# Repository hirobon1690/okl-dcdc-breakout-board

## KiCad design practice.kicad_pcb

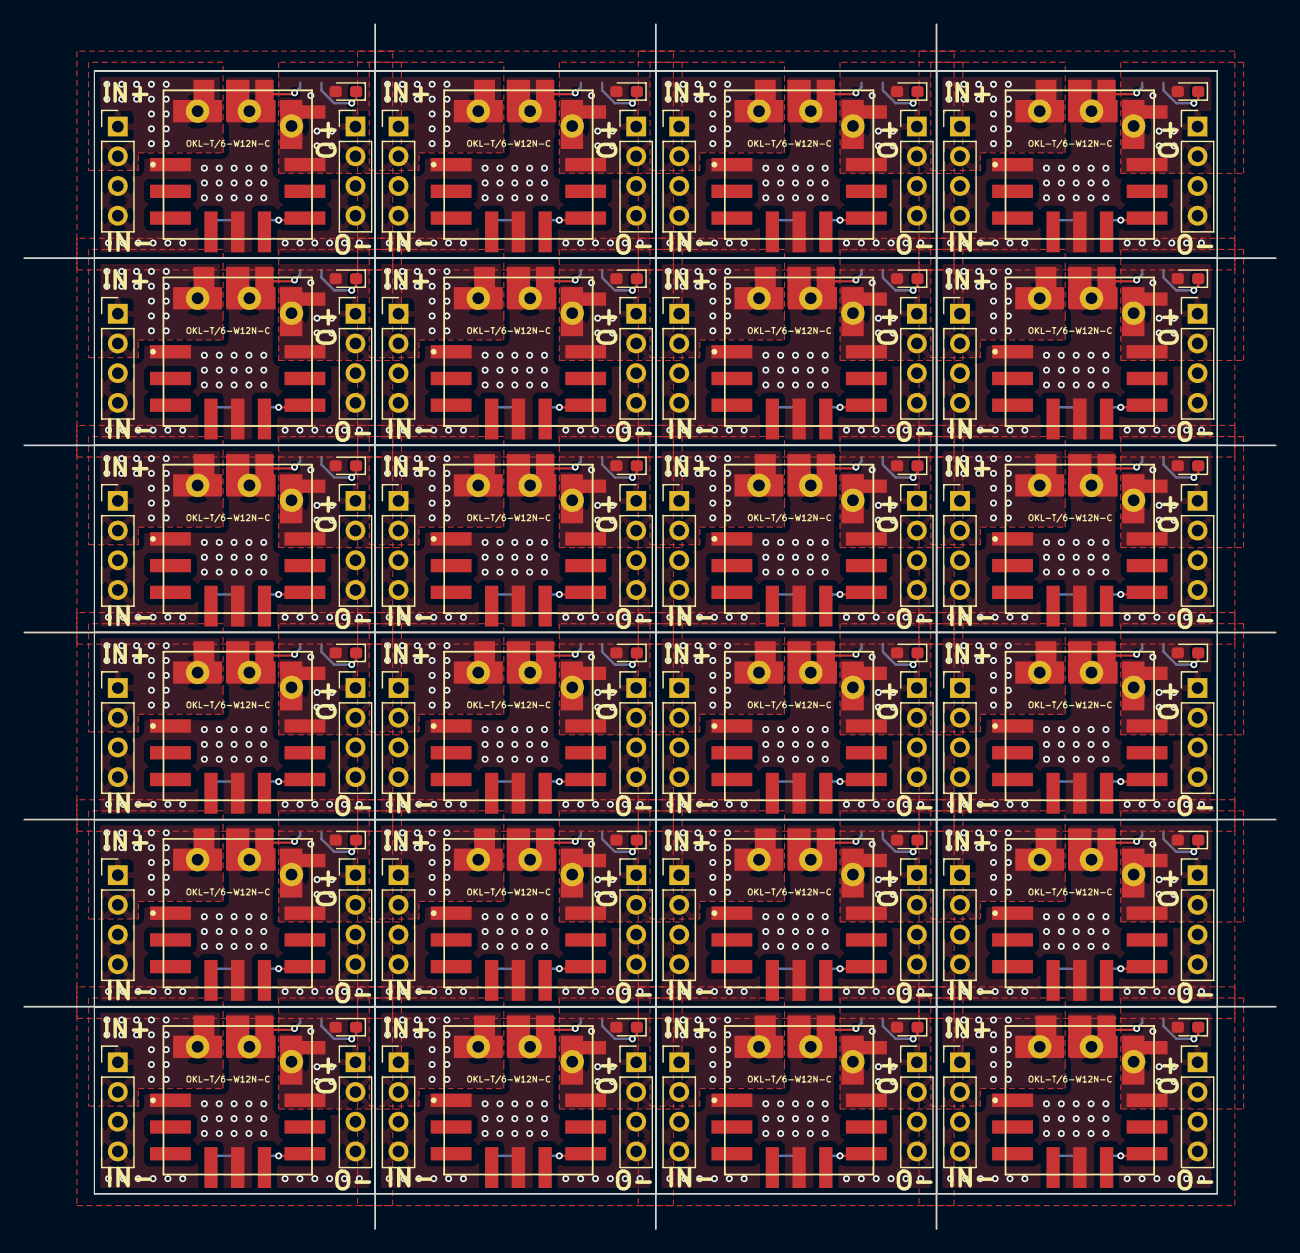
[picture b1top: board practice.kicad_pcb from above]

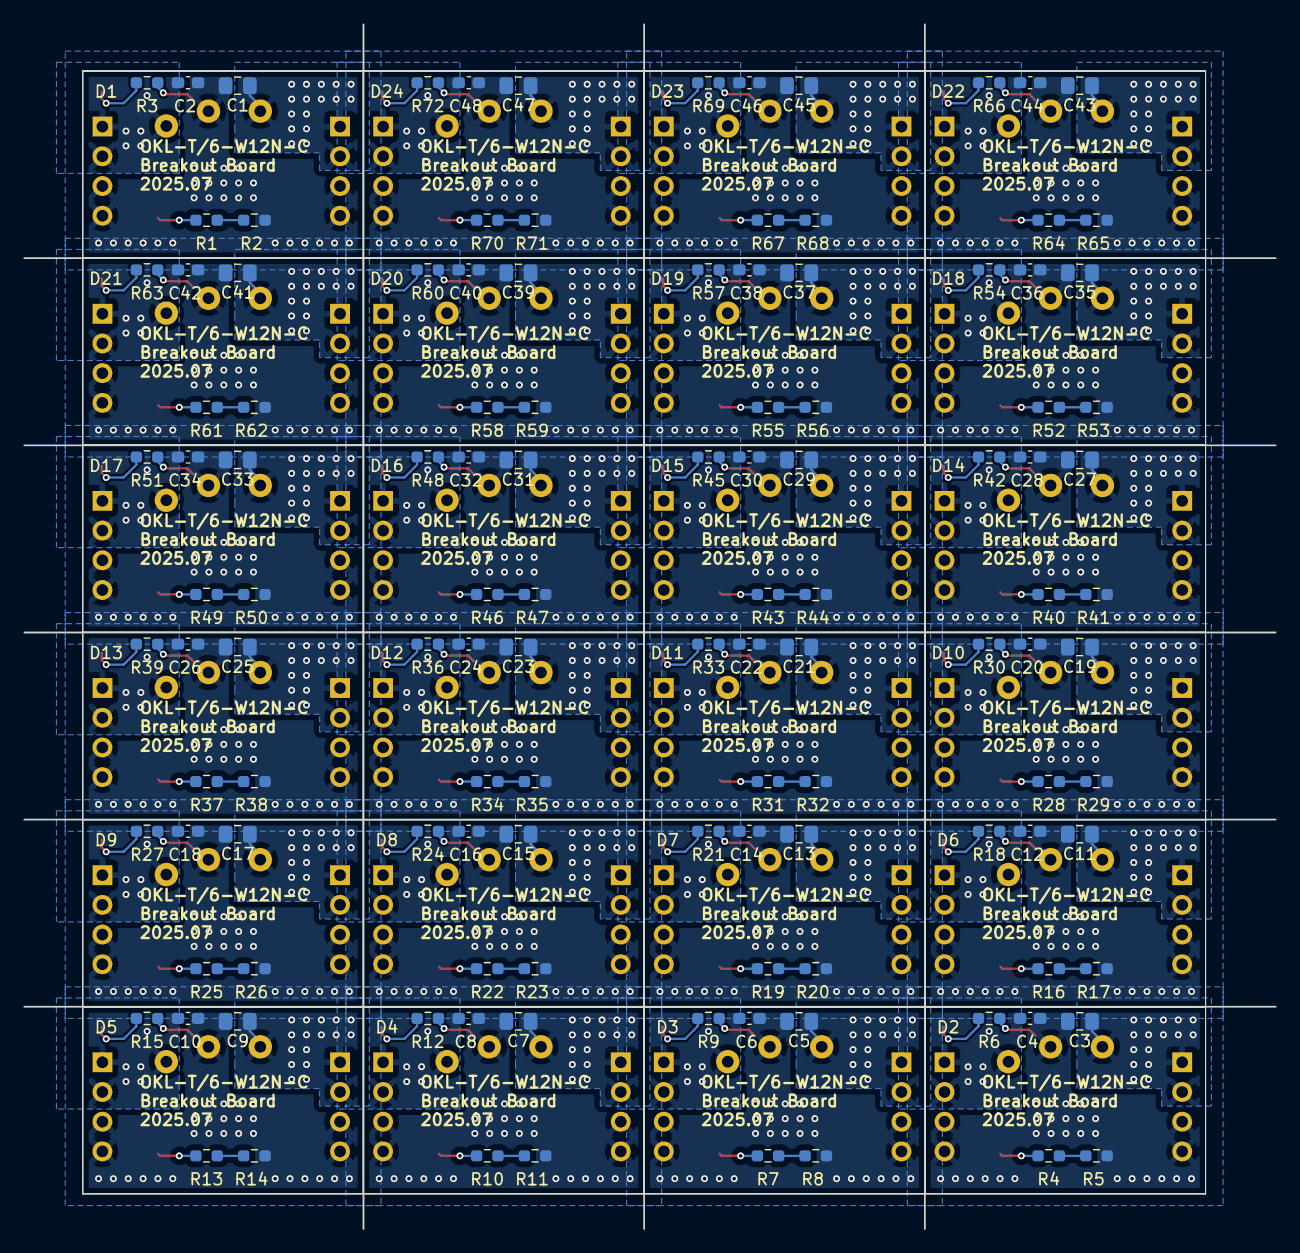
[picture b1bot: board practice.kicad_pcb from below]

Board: 2 copper layers, 107.0 x 103.0 mm, 216 parts (120 on the bottom side), 6 nets.

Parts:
C1, C3, C5, C7, C9, C11, C13, C15, C17, C19, C21, C23, C25, C27, C29, C31, C33, C35, C37, C39, C41, C43, C45, C47: 22u; C_0805_2012Metric_Pad1.18x1.45mm_HandSolder
C2, C4, C6, C8, C10, C12, C14, C16, C18, C20, C22, C24, C26, C28, C30, C32, C34, C36, C38, C40, C42, C44, C46, C48: 10u; C_0603_1608Metric_Pad1.08x0.95mm_HandSolder
D1, D2, D3, D4, D5, D6, D7, D8, D9, D10, D11, D12, D13, D14, D15, D16, D17, D18, D19, D20, D21, D22, D23, D24: LED; LED_0603_1608Metric_Pad1.05x0.95mm_HandSolder
J1, J2, J3, J4, J5, J6, J7, J8, J9, J10, J11, J12, J13, J14, J15, J16, J17, J18, J19, J20, J21, J22, J23, J24, J25, J26, J27, J28, J29, J30, J31, J32, J33, J34, J35, J36, J37, J38, J39, J40, J41, J42, J43, J44, J45, J46, J47, J48: Conn_01x04_Pin; PinHeader_1x04_P2.54mm_Vertical
MD1, MD2, MD3, MD4, MD5, MD6, MD7, MD8, MD9, MD10, MD11, MD12, MD13, MD14, MD15, MD16, MD17, MD18, MD19, MD20, MD21, MD22, MD23, MD24: OKL-T_6-W12N-C; MURATA_OKL-T-6-W12N-C_0
R1, R3, R4, R6, R7, R9, R10, R12, R13, R15, R16, R18, R19, R21, R22, R24, R25, R27, R28, R30, R31, R33, R34, R36, R37, R39, R40, R42, R43, R45, R46, R48, R49, R51, R52, R54, R55, R57, R58, R60, R61, R63, R64, R66, R67, R69, R70, R72: 1.2k; R_0603_1608Metric_Pad0.98x0.95mm_HandSolder
R2, R5, R8, R11, R14, R17, R20, R23, R26, R29, R32, R35, R38, R41, R44, R47, R50, R53, R56, R59, R62, R65, R68, R71: 120; R_0603_1608Metric_Pad0.98x0.95mm_HandSolder

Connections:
+5V: C2.1, C4.1, C6.1, C8.1, C10.1, C12.1, C14.1, C16.1, C18.1, C20.1, C22.1, C24.1, C26.1, C28.1, C30.1, C32.1, C34.1, C36.1, C38.1, C40.1, C42.1, C44.1, C46.1, C48.1, D1.2 (A), D2.2 (A), D3.2 (A), D4.2 (A), D5.2 (A), D6.2 (A), D7.2 (A), D8.2 (A), D9.2 (A), D10.2 (A), D11.2 (A), D12.2 (A), D13.2 (A), D14.2 (A), D15.2 (A), D16.2 (A), D17.2 (A), D18.2 (A), D19.2 (A), D20.2 (A), D21.2 (A), D22.2 (A), D23.2 (A), D24.2 (A), J2.1, J2.2, J4.1, J4.2, J6.1, J6.2, J8.1, J8.2, J10.1, J10.2, J12.1, J12.2, J14.1, J14.2, J16.1, J16.2, J18.1, J18.2, J20.1, J20.2, J22.1, J22.2, J24.1, J24.2, J26.1, J26.2, J28.1, J28.2, J30.1, J30.2, J32.1, J32.2, J34.1, J34.2, J36.1, J36.2, J38.1, J38.2, J40.1, J40.2, J42.1, J42.2, J44.1, J44.2, J46.1, J46.2, J48.1, J48.2, MD1.4 (VOUT), MD1.5 (SENSE), MD2.4 (VOUT), MD2.5 (SENSE), MD3.4 (VOUT), MD3.5 (SENSE), MD4.4 (VOUT), MD4.5 (SENSE), MD5.4 (VOUT), MD5.5 (SENSE), MD6.4 (VOUT), MD6.5 (SENSE), MD7.4 (VOUT), MD7.5 (SENSE), MD8.4 (VOUT), MD8.5 (SENSE), MD9.4 (VOUT), MD9.5 (SENSE), MD10.4 (VOUT), MD10.5 (SENSE), MD11.4 (VOUT), MD11.5 (SENSE), MD12.4 (VOUT), MD12.5 (SENSE), MD13.4 (VOUT), MD13.5 (SENSE), MD14.4 (VOUT), MD14.5 (SENSE), MD15.4 (VOUT), MD15.5 (SENSE), MD16.4 (VOUT), MD16.5 (SENSE), MD17.4 (VOUT), MD17.5 (SENSE), MD18.4 (VOUT), MD18.5 (SENSE), MD19.4 (VOUT), MD19.5 (SENSE), MD20.4 (VOUT), MD20.5 (SENSE), MD21.4 (VOUT), MD21.5 (SENSE), MD22.4 (VOUT), MD22.5 (SENSE), MD23.4 (VOUT), MD23.5 (SENSE), MD24.4 (VOUT), MD24.5 (SENSE)
+BATT: C1.1, C3.1, C5.1, C7.1, C9.1, C11.1, C13.1, C15.1, C17.1, C19.1, C21.1, C23.1, C25.1, C27.1, C29.1, C31.1, C33.1, C35.1, C37.1, C39.1, C41.1, C43.1, C45.1, C47.1, J1.1, J1.2, J3.1, J3.2, J5.1, J5.2, J7.1, J7.2, J9.1, J9.2, J11.1, J11.2, J13.1, J13.2, J15.1, J15.2, J17.1, J17.2, J19.1, J19.2, J21.1, J21.2, J23.1, J23.2, J25.1, J25.2, J27.1, J27.2, J29.1, J29.2, J31.1, J31.2, J33.1, J33.2, J35.1, J35.2, J37.1, J37.2, J39.1, J39.2, J41.1, J41.2, J43.1, J43.2, J45.1, J45.2, J47.1, J47.2, MD1.2 (VIN), MD2.2 (VIN), MD3.2 (VIN), MD4.2 (VIN), MD5.2 (VIN), MD6.2 (VIN), MD7.2 (VIN), MD8.2 (VIN), MD9.2 (VIN), MD10.2 (VIN), MD11.2 (VIN), MD12.2 (VIN), MD13.2 (VIN), MD14.2 (VIN), MD15.2 (VIN), MD16.2 (VIN), MD17.2 (VIN), MD18.2 (VIN), MD19.2 (VIN), MD20.2 (VIN), MD21.2 (VIN), MD22.2 (VIN), MD23.2 (VIN), MD24.2 (VIN)
GND: C1.2, C2.2, C3.2, C4.2, C5.2, C6.2, C7.2, C8.2, C9.2, C10.2, C11.2, C12.2, C13.2, C14.2, C15.2, C16.2, C17.2, C18.2, C19.2, C20.2, C21.2, C22.2, C23.2, C24.2, C25.2, C26.2, C27.2, C28.2, C29.2, C30.2, C31.2, C32.2, C33.2, C34.2, C35.2, C36.2, C37.2, C38.2, C39.2, C40.2, C41.2, C42.2, C43.2, C44.2, C45.2, C46.2, C47.2, C48.2, J1.3, J1.4, J2.3, J2.4, J3.3, J3.4, J4.3, J4.4, J5.3, J5.4, J6.3, J6.4, J7.3, J7.4, J8.3, J8.4, J9.3, J9.4, J10.3, J10.4, J11.3, J11.4, J12.3, J12.4, J13.3, J13.4, J14.3, J14.4, J15.3, J15.4, J16.3, J16.4, J17.3, J17.4, J18.3, J18.4, J19.3, J19.4, J20.3, J20.4, J21.3, J21.4, J22.3, J22.4, J23.3, J23.4, J24.3, J24.4, J25.3, J25.4, J26.3, J26.4, J27.3, J27.4, J28.3, J28.4, J29.3, J29.4, J30.3, J30.4, J31.3, J31.4, J32.3, J32.4, J33.3, J33.4, J34.3, J34.4, J35.3, J35.4, J36.3, J36.4, J37.3, J37.4, J38.3, J38.4, J39.3, J39.4, J40.3, J40.4, J41.3, J41.4, J42.3, J42.4, J43.3, J43.4, J44.3, J44.4, J45.3, J45.4, J46.3, J46.4, J47.3, J47.4, J48.3, J48.4, MD1.1 (~ON/OFF_CONTROL), MD1.3 (1_GROUND), MD1.7 (2_GROUND), MD2.1 (~ON/OFF_CONTROL), MD2.3 (1_GROUND), MD2.7 (2_GROUND), MD3.1 (~ON/OFF_CONTROL), MD3.3 (1_GROUND), MD3.7 (2_GROUND), MD4.1 (~ON/OFF_CONTROL), MD4.3 (1_GROUND), MD4.7 (2_GROUND), MD5.1 (~ON/OFF_CONTROL), MD5.3 (1_GROUND), MD5.7 (2_GROUND), MD6.1 (~ON/OFF_CONTROL), MD6.3 (1_GROUND), MD6.7 (2_GROUND), MD7.1 (~ON/OFF_CONTROL), MD7.3 (1_GROUND), MD7.7 (2_GROUND), MD8.1 (~ON/OFF_CONTROL), MD8.3 (1_GROUND), MD8.7 (2_GROUND), MD9.1 (~ON/OFF_CONTROL), MD9.3 (1_GROUND), MD9.7 (2_GROUND), MD10.1 (~ON/OFF_CONTROL), MD10.3 (1_GROUND), MD10.7 (2_GROUND), MD11.1 (~ON/OFF_CONTROL), MD11.3 (1_GROUND), MD11.7 (2_GROUND), MD12.1 (~ON/OFF_CONTROL), MD12.3 (1_GROUND), MD12.7 (2_GROUND), MD13.1 (~ON/OFF_CONTROL), MD13.3 (1_GROUND), MD13.7 (2_GROUND), MD14.1 (~ON/OFF_CONTROL), MD14.3 (1_GROUND), MD14.7 (2_GROUND), MD15.1 (~ON/OFF_CONTROL), MD15.3 (1_GROUND), MD15.7 (2_GROUND), MD16.1 (~ON/OFF_CONTROL), MD16.3 (1_GROUND), MD16.7 (2_GROUND), MD17.1 (~ON/OFF_CONTROL), MD17.3 (1_GROUND), MD17.7 (2_GROUND), MD18.1 (~ON/OFF_CONTROL), MD18.3 (1_GROUND), MD18.7 (2_GROUND), MD19.1 (~ON/OFF_CONTROL), MD19.3 (1_GROUND), MD19.7 (2_GROUND), MD20.1 (~ON/OFF_CONTROL), MD20.3 (1_GROUND), MD20.7 (2_GROUND), MD21.1 (~ON/OFF_CONTROL), MD21.3 (1_GROUND), MD21.7 (2_GROUND), MD22.1 (~ON/OFF_CONTROL), MD22.3 (1_GROUND), MD22.7 (2_GROUND), MD23.1 (~ON/OFF_CONTROL), MD23.3 (1_GROUND), MD23.7 (2_GROUND), MD24.1 (~ON/OFF_CONTROL), MD24.3 (1_GROUND), MD24.7 (2_GROUND), R2.2, R3.2, R5.2, R6.2, R8.2, R9.2, R11.2, R12.2, R14.2, R15.2, R17.2, R18.2, R20.2, R21.2, R23.2, R24.2, R26.2, R27.2, R29.2, R30.2, R32.2, R33.2, R35.2, R36.2, R38.2, R39.2, R41.2, R42.2, R44.2, R45.2, R47.2, R48.2, R50.2, R51.2, R53.2, R54.2, R56.2, R57.2, R59.2, R60.2, R62.2, R63.2, R65.2, R66.2, R68.2, R69.2, R71.2, R72.2
unnamed: D1.1 (K), D2.1 (K), D3.1 (K), D4.1 (K), D5.1 (K), D6.1 (K), D7.1 (K), D8.1 (K), D9.1 (K), D10.1 (K), D11.1 (K), D12.1 (K), D13.1 (K), D14.1 (K), D15.1 (K), D16.1 (K), D17.1 (K), D18.1 (K), D19.1 (K), D20.1 (K), D21.1 (K), D22.1 (K), D23.1 (K), D24.1 (K), R3.1, R6.1, R9.1, R12.1, R15.1, R18.1, R21.1, R24.1, R27.1, R30.1, R33.1, R36.1, R39.1, R42.1, R45.1, R48.1, R51.1, R54.1, R57.1, R60.1, R63.1, R66.1, R69.1, R72.1
unnamed: MD1.6 (TRIM), MD2.6 (TRIM), MD3.6 (TRIM), MD4.6 (TRIM), MD5.6 (TRIM), MD6.6 (TRIM), MD7.6 (TRIM), MD8.6 (TRIM), MD9.6 (TRIM), MD10.6 (TRIM), MD11.6 (TRIM), MD12.6 (TRIM), MD13.6 (TRIM), MD14.6 (TRIM), MD15.6 (TRIM), MD16.6 (TRIM), MD17.6 (TRIM), MD18.6 (TRIM), MD19.6 (TRIM), MD20.6 (TRIM), MD21.6 (TRIM), MD22.6 (TRIM), MD23.6 (TRIM), MD24.6 (TRIM), R1.1, R4.1, R7.1, R10.1, R13.1, R16.1, R19.1, R22.1, R25.1, R28.1, R31.1, R34.1, R37.1, R40.1, R43.1, R46.1, R49.1, R52.1, R55.1, R58.1, R61.1, R64.1, R67.1, R70.1
unnamed: R1.2, R2.1, R4.2, R5.1, R7.2, R8.1, R10.2, R11.1, R13.2, R14.1, R16.2, R17.1, R19.2, R20.1, R22.2, R23.1, R25.2, R26.1, R28.2, R29.1, R31.2, R32.1, R34.2, R35.1, R37.2, R38.1, R40.2, R41.1, R43.2, R44.1, R46.2, R47.1, R49.2, R50.1, R52.2, R53.1, R55.2, R56.1, R58.2, R59.1, R61.2, R62.1, R64.2, R65.1, R67.2, R68.1, R70.2, R71.1
